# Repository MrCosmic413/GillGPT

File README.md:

# GillGPT — Meet Kevin 🐟

Kevin is an AI-powered animatronic fish built by modifying a Big Mouth Billy Bass. GillGPT brings together conversational AI, speech recognition, synthesized speech, a Raspberry Pi, FPGA motor control, and a custom KiCad PCB.

The project has grown from reverse-engineering two motors into an integrated hardware/software build: Kevin speaks, moves his mouth with the audio, and shows activity on an LCD.

## How it works

```text
Microphone → Raspberry Pi / KevinOS → PC speech recognition
                        ↓
                   Ollama response
                        ↓
                  Kokoro speech → Speaker
                        ↓
              Mouth animation + LCD feedback
                        ↓
       UART → Tang Nano 9K FPGA → TB6612FNG → Motors
```

The Raspberry Pi coordinates the interaction. The PC provides AI and speech services. The Tang Nano 9K handles timed motor sequences in Verilog, with the TB6612FNG driving the mouth and shared head/tail mechanism.

## Build status — September 20, 2026

- Original mechanism reverse engineered; motor direction and wiring documented.
- Custom KiCad schematic, PCB layout, and module footprints added.
- FPGA UART, PWM, mouth animation, head return, tail movement, and stop command implemented in source.
- Voice, LCD feedback, and mouth movement reported working in the latest integration session.
- Head/tail motor interference remains under investigation: disconnecting J3 restored clean audio in the latest test. The precise electrical cause and final fix still need verification.
- Full completion video will be added after the remaining fixes and final demonstration.

**Source coverage:** the FPGA and hardware files are recovered from the local project. PC service source is included. The available Pi backup is dated **August 19, 2026** and is preserved as an explicitly dated snapshot; it does **not** contain all September changes or the latest LCD integration. See [source provenance and outstanding work](docs/STATUS.md).

## Explore the project

| Area | Files |
| --- | --- |
| Editable schematic and PCB | [KiCad project](hardware/kicad/Kevin_PCB.kicad_pro), [schematic](hardware/kicad/Kevin_PCB.kicad_sch), [PCB](hardware/kicad/Kevin_PCB.kicad_pcb) |
| Custom module footprints | [Kevin.pretty](hardware/kicad/Kevin.pretty) |
| Manufacturing exports | [Saved Gerber sets](hardware/fabrication) |
| Main FPGA controller | [Verilog](firmware/Kevin_motor_controller/src/kevin_motor_controller.v), [pin constraints](firmware/Kevin_motor_controller/src/kevin_motor_controller.cst), [Gowin project](firmware/Kevin_motor_controller/Kevin_motor_controller.gprj) |
| Earlier FPGA bring-up | [Mouth test](firmware/Kevin_motor_test), [UART](firmware/kevin_nano_uart), [LED blink](firmware/kevin_nano_blink) |
| PC voice and integration services | [PC software](software/pc) |
| Historical Pi code | [KevinOS — August 19 snapshot](software/archive/2026-08-19/KevinOS) |
| Original motor investigation | [Reverse-engineering notes](docs/REV001_ReverseEngineering.md) |

## Hardware and firmware

Open `hardware/kicad/Kevin_PCB.kicad_pro` in KiCad. Keep `Kevin.pretty` and `fp-lib-table` alongside the project so its custom footprints resolve. Saved fabrication exports are historical sets; their correspondence to the current board has not been verified. Regenerate fabrication files from a checked board before ordering.

Open the main controller `.gprj` in Gowin for the Tang Nano 9K. Source defaults assume a 27 MHz clock, approximately 115200-baud UART, and 1 kHz PWM. Motor timing and duty-cycle constants are specific to this mechanism.

| UART byte | Action |
| --- | --- |
| `q`, `n`, `N`, `e`, `E` | Quiet, normal short/long, and emphasis short/long mouth sequences |
| `H` | Head out |
| `h` | Head home |
| `T` | Tail sequence |
| `S` | Stop |

Acknowledgements identify recognized commands; they do not prove physical movement completed. The early reverse-engineering notes use motor labels from the original investigation; the main FPGA source calls the mouth channel A and head/tail channel B.

## Software

See [PC service setup](software/pc/README.md). The services cover Kokoro speech synthesis, faster-whisper transcription, and an optional Spotify/file-access bridge. Ollama supplies the language-model endpoint used by KevinOS.

The dated Pi snapshot is useful for understanding the earlier audio, AI, and motor architecture. It is not a complete reproduction of the present build. The current Pi source, dependency versions, and final demonstration remain to be synchronized.

## Validation

For this repository update, Python sources were checked for syntax and the main Verilog controller was compiled with Icarus Verilog. These checks do not establish hardware operation, timing closure, electrical correctness, or completion of the remaining integration fixes.

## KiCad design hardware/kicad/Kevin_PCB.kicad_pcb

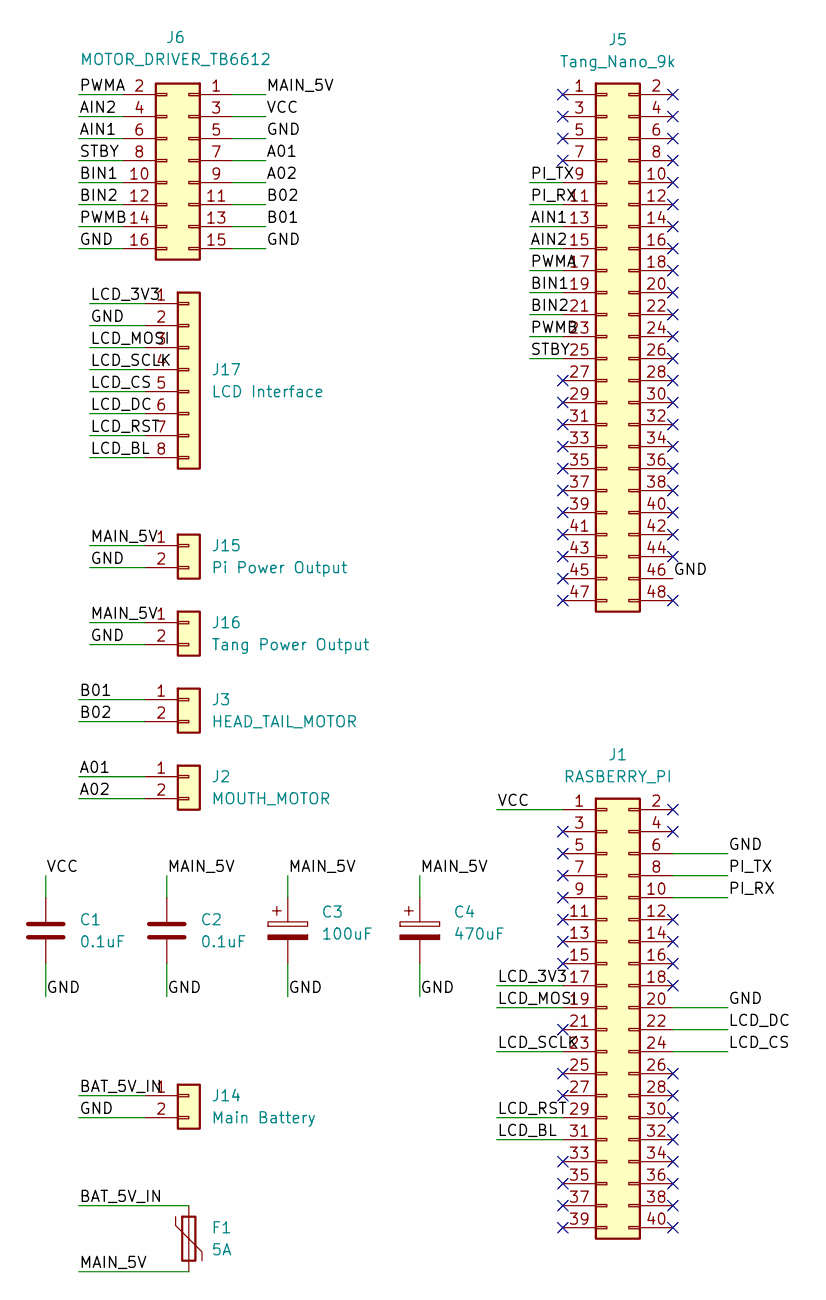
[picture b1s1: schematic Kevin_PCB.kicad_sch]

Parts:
C1, C2: 0.1uF; C_0805_2012Metric
C3: 100uF; CP_Radial_D6.3mm_P2.50mm
C4: 470uF; CP_Radial_D8.0mm_P3.50mm
F1: 5A; Fuse_Bourns_MF-RG300
J1: RASBERRY_PI; PinSocket_2x20_P2.54mm_Vertical
J2: MOUTH_MOTOR; TerminalBlock_Phoenix_MKDS-1,5-2-5.08_1x02_P5.08mm_Horizont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
J3: HEAD_TAIL_MOTOR; TerminalBlock_Phoenix_MKDS-1,5-2-5.08_1x02_P5.08mm_Horizont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
J5: Tang_Nano_9k; Tang_Nano_9K_Module
J6: MOTOR_DRIVER_TB6612; TB6612_Module_2x8_15mm
J14: Main Battery; TerminalBlock_Phoenix_MKDS-1,5-2-5.08_1x02_P5.08mm_Horizont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
J15: Pi Power Output; TerminalBlock_Phoenix_MKDS-1,5-2-5.08_1x02_P5.08mm_Horizont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
J16: Tang Power Output; TerminalBlock_Phoenix_MKDS-1,5-2-5.08_1x02_P5.08mm_Horizont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
J17: LCD Interface; PinHeader_1x08_P2.54mm_Vertical

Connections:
/A01: J2.1, J6.7
/A02: J2.2, J6.9
/AIN1: J5.13, J6.6
/AIN2: J5.15, J6.4
/B01: J3.1, J6.13
/B02: J3.2, J6.11
/BAT_5V_IN: F1.1, J14.1
/BIN1: J5.19, J6.10
/BIN2: J5.21, J6.12
/GND: C1.2, C2.2, C3.2, C4.2, J1.6, J1.20, J5.46, J6.5, J6.15, J6.16, J14.2, J15.2, J16.2, J17.2
/LCD_3V3: J1.17, J17.1
/LCD_BL: J1.31, J17.8
/LCD_CS: J1.24, J17.5
/LCD_DC: J1.22, J17.6
/LCD_MOSI: J1.19, J17.3
/LCD_RST: J1.29, J17.7
/LCD_SCLK: J1.23, J17.4
/MAIN_5V: C2.1, C3.1, C4.1, F1.2, J6.1, J15.1, J16.1
/PI_RX: J1.10, J5.11
/PI_TX: J1.8, J5.9
/PWMA: J5.17, J6.2
/PWMB: J5.23, J6.14
/STBY: J5.25, J6.8
/VCC: C1.1, J1.1, J6.3

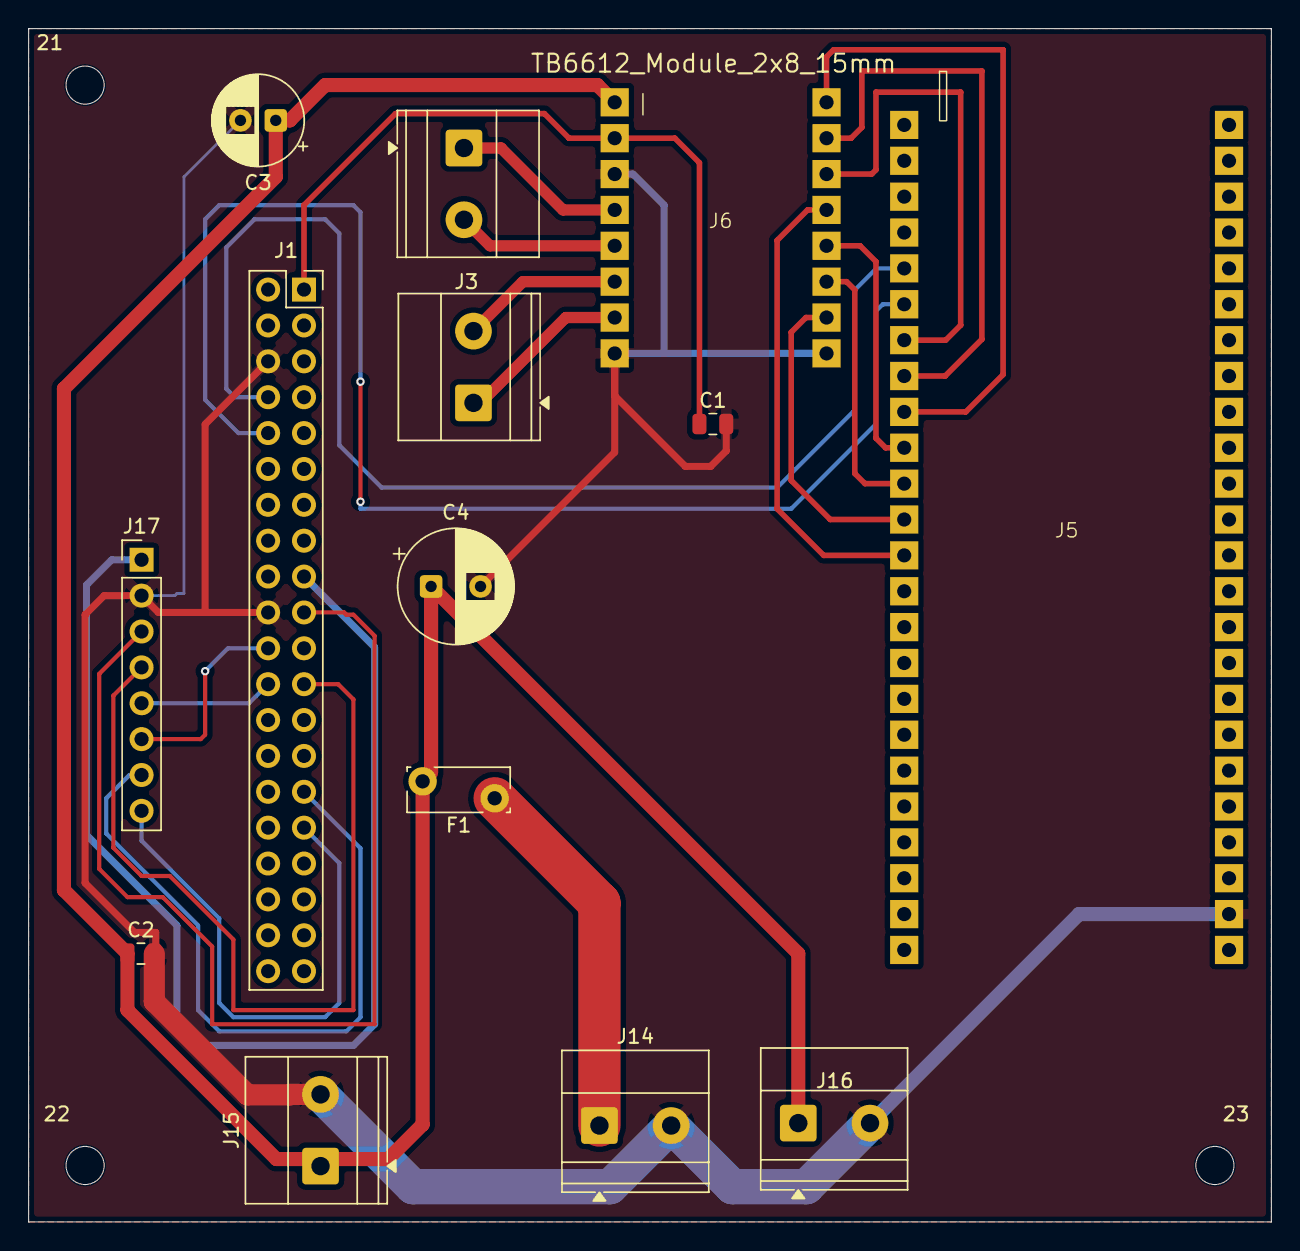
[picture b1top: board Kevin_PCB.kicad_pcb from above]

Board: 2 copper layers, 88.0 x 84.5 mm, 17 parts (0 on the bottom side), 24 nets.

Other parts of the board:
21, 22, 23: MountingHole_2.7mm_M2.5
